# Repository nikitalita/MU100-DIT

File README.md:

# MU100-DIT

A modification for Yamaha synthesizers to add optical audio out.

This mod has been especially designed for: 
* Yamaha MU100
* Yamaha MU100R
* Yamaha MU90
* Yamaha MU90R

For these synths, a connector board has been designed that enables this mod to be installed with little-to-no board modification.

On the MU100/MU90, this involves soldering an unpopulated header and bridging some pads.

On the Rackmount versions of these, the MU100R/MU90R, this will plug in directly to the molex connector for the analog board, no board modification required:

The main board has been designed to fit within the limited back panel space on the MU100/MU90 and to not run into the MU100/MU100R's expansion cards.

## Schematics:

### Main board

### MU100/MU90 Connector board

## Installation instructions:

For the Yamaha MU100/MU90, the DIF0 must be bridged, all others left floating.

**TODO: Rest of instructions**

## Other compatible synths
This includes the following synthesizers:

* Yamaha MU128
* Yamaha AN200

...and many others. This mod will work for any device that has a 16-bit, 18-bit, 20-bit, or 24-bit PCM/I2S data stream feeding into the DAC, and has a consistent sample rate of 32/44.1/48/88.2/96khz. If you would like to test this out on other devices, please feel free to submit a pull request detailing what device and what settings you set.

## Links:
* https://esher.ru/blog/887.html - The main inspiration for this design, special thanks to vetal!
* https://github.com/vetal-esher/18bit-DIT - Vetal's custom AK4103A board that is designed to use coax with a transformer instead of optical.
* https://kurohane.net/wiki/index.php?SC-88Pro%E3%81%AB%E5%85%89%E3%83%87%E3%82%B8%E3%82%BF%E3%83%AB%E5%87%BA%E5%8A%9B%E3%82%92%E4%BB%98%E3%81%91%E3%82%8B (Japanese) - Another AK4103A optical mod, designed for the SC-88 pro.
* https://github.com/w-dee/AK4103A-DIT - Another, general purpose AK4103A DIT modification.

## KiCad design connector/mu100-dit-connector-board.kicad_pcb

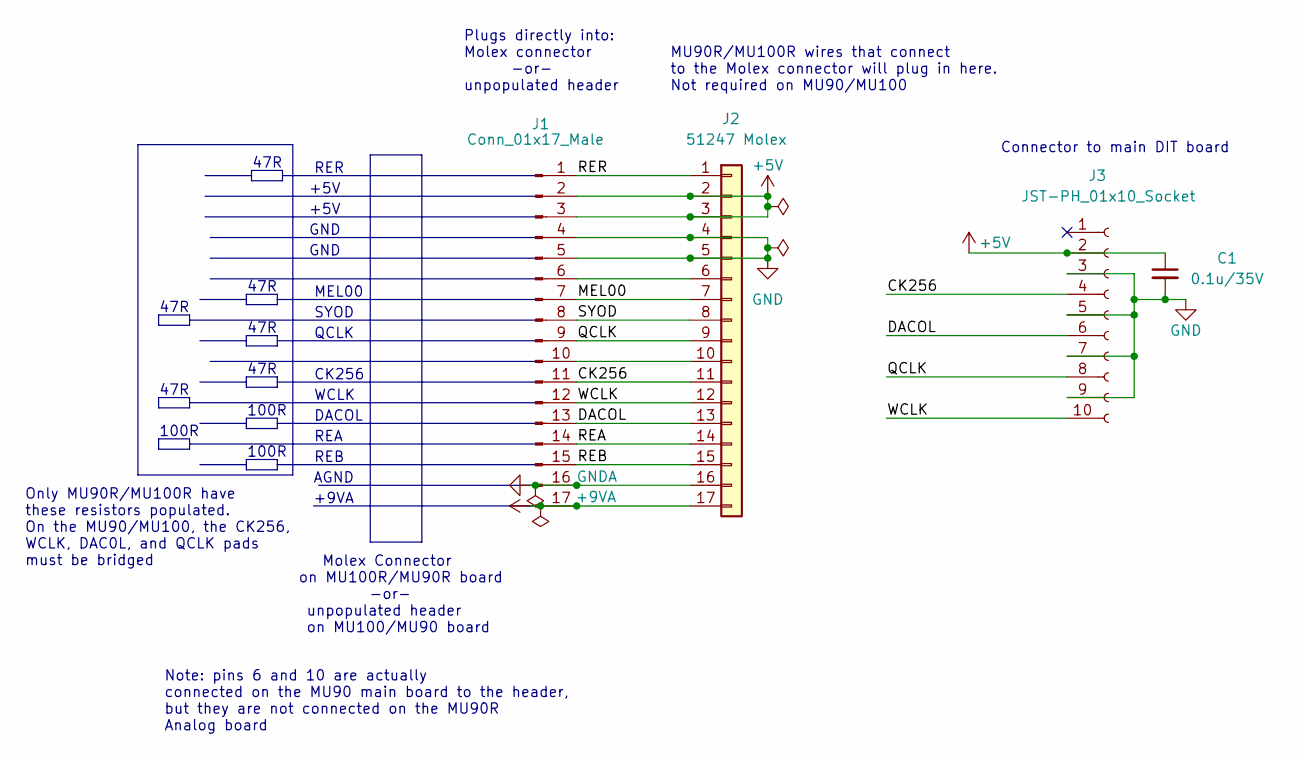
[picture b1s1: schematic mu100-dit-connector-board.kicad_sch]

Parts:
C1: 0.1u/35V; C_0805_2012Metric_Pad1.18x1.45mm_HandSolder
J1: Conn_01x17_Male; PinHeader_1x17_P2.00mm_Vertical
J2: 51247 Molex; Molex_Wire-Trap_52147-1710_1x17_P2.00mm_Vertical; Mfg. Part No. 0521471710; Mouser 538-52147-1710
J3: JST-PH_01x10_Socket; JST_PH_B10B-PH-K_1x10_P2.00mm_Vertical

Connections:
+5V: C1.1, J1.2, J1.3, J2.2, J2.3, J3.2
+9VA: J1.17, J2.17
/CK256: J1.11, J2.11, J3.4
/DACOL: J1.13, J2.13, J3.6
/MEL00: J1.7, J2.7
/QCLK: J1.9, J2.9, J3.8
/REA: J1.14, J2.14
/REB: J1.15, J2.15
/RER: J1.1, J2.1
/SYOD: J1.8, J2.8
/WCLK: J1.12, J2.12, J3.10
GND: C1.2, J1.4, J1.5, J2.4, J2.5, J3.3, J3.5, J3.7, J3.9
GNDA: J1.16, J2.16
unnamed: J1.6, J2.6
unnamed: J1.10, J2.10

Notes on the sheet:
100R
Only MU90R/MU100R have these resistors populated. On the MU90/MU100, the CK256, WCLK, DAC0L, and QCLK pads must be bridged
+5V
Note: pins 6 and 10 are actually connected on the MU90 main board to the header, but they are not connected on the MU90R Analog board
REB
47R
+9VA
CK256
SYOD
DACOL
GND
QCLK
Plugs directly into: Molex connector -or- unpopulated header
Molex Connector on MU100R/MU90R board -or- unpopulated header on MU100/MU90 board
MEL00
REA
RER
Connector to main DIT board
AGND
WCLK
MU90R/MU100R wires that connect to the Molex connector will plug in here. Not required on MU90/MU100

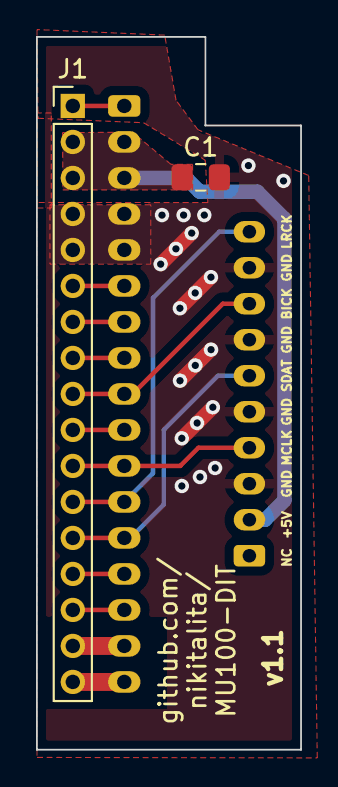
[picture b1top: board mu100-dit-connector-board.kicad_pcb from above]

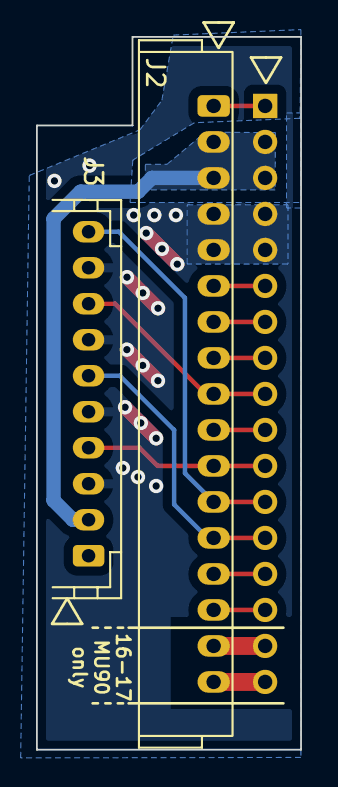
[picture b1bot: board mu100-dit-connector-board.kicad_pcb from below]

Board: 2 copper layers, 14.7 x 39.6 mm, 4 parts (2 on the bottom side), 15 nets.

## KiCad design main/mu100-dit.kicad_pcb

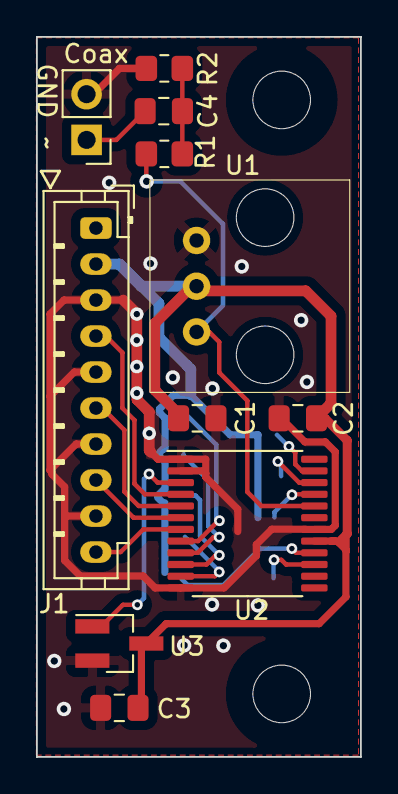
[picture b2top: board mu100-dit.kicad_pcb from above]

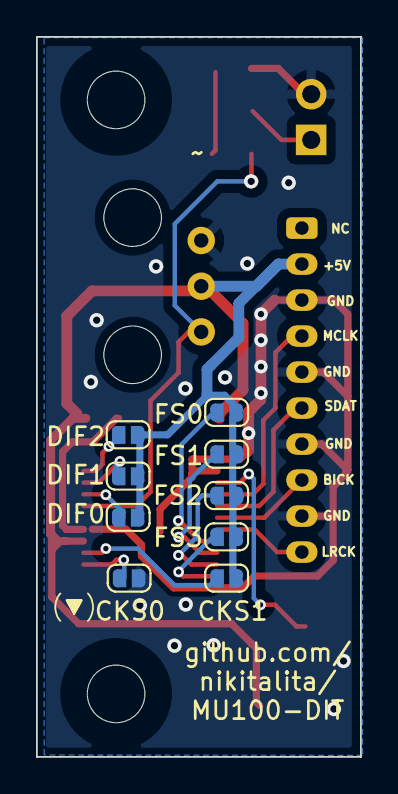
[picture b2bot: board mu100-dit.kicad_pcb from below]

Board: 2 copper layers, 18.0 x 40.0 mm, 22 parts (9 on the bottom side), 19 nets.

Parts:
C1, C2, C3, C4: 0.1uF; C_0805_2012Metric_Pad1.18x1.45mm_HandSolder
H1, H2: MountingHole_Pad; MountingHole_3.2mm_M3_ISO7380
J1: Conn_01x10_Female; JST_PH_B10B-PH-K_1x10_P2.00mm_Vertical
J2: Conn_01x02_Male; PinHeader_1x02_P2.54mm_Vertical
JP1, JP2, JP3, JP4, JP5, JP6, JP7, JP8, JP9: Jumper_NO_Small; SolderJumper-Open_RoundedPad-custom
R1: 330; R_0805_2012Metric_Pad1.20x1.40mm_HandSolder
R2: 100; R_0805_2012Metric_Pad1.20x1.40mm_HandSolder
U1: TOTX-177L; Toshiba_TOTX177
U2: AK4103A; TSSOP-24_6.1x7.8mm_P0.65mm
U3: APX809S-46SR-7; SOT-23_Handsoldering

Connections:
+5V: C1.2, C2.2, C3.2, J1.2, JP1.1, JP2.1, JP3.1, JP4.1, JP5.1, JP6.1, JP7.1, JP9.1, U1.2 (VCC), U2.17 (VDD), U3.3 (VCC)
/BICK: J1.8, U2.6 (BICK)
/CKS0: JP8.2, U2.15 (CKS0)
/CKS1: JP9.2, U2.16 (CKS1)
/DIF0: JP5.2, U2.21 (DIF0)
/DIF1: JP6.2, U2.22 (DIF1)
/DIF2: JP7.2, U2.23 (DIF2)
/FS0: JP1.2, U2.8 (FS0/CSN)
/FS1: JP2.2, U2.9 (FS1/CDTI)
/FS2: JP3.2, U2.10 (FS2/CCLK)
/FS3: JP4.2, U2.11 (FS3/CDTO)
/LRCK: J1.10, U2.7 (LRCK)
/MCLK: J1.4, U2.4 (MCLK)
/RESET: U2.3 (PDN), U3.1 (~RESET)
/SDAT: J1.6, U2.5 (SDTI)
/TXP: R1.1, U1.3 (Input), U2.20 (TXP)
GND: C1.1, C2.1, C3.1, J1.3, J1.5, J1.7, J1.9, J2.2, JP8.1, R2.1, U1.1 (GND), U2.1 (V1), U2.2 (TRANS), U2.12 (C1), U2.18 (VSS), U3.2 (GND)
unnamed: C4.1, R1.2, R2.2
unnamed: C4.2, J2.1

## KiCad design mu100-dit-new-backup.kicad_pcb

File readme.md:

From https://kurohane.net/wiki/index.php?SC-88Pro%E3%81%AB%E5%85%89%E3%83%87%E3%82%B8%E3%82%BF%E3%83%AB%E5%87%BA%E5%8A%9B%E3%82%92%E4%BB%98%E3%81%91%E3%82%8B

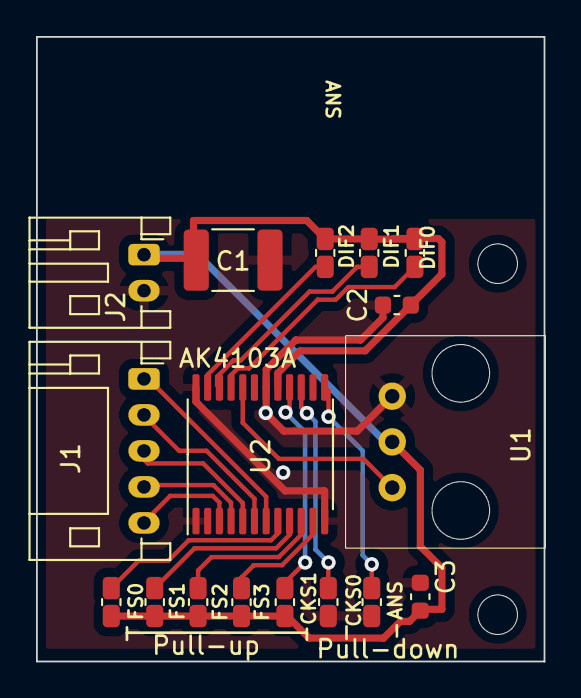
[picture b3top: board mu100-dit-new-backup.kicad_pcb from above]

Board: 2 copper layers, 28.2 x 34.7 mm, 17 parts (0 on the bottom side), 18 nets.

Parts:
C1: 33u/16v; C_1812_4532Metric
C2, C3: 0.1u/35V; C_0603_1608Metric
J1: Conn_01x05_Male; JST_PH_S5B-PH-K_1x05_P2.00mm_Horizontal
J2: Conn_01x02_Male; JST_PH_S2B-PH-K_1x02_P2.00mm_Horizontal
JP1, JP2, JP3, JP9, JP11, JP14, JP15, JP16, JP17, JP18: Jumper_NO_Small; R_0603_1608Metric_SolderJumperCompatible
U1: TOTX-177L; Toshiba_TOTX177
U2: AK4103A; TSSOP-24_6.1x7.8mm_P0.65mm

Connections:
+5V: C1.1, C2.2, C3.2, J2.1, JP1.1, JP2.1, JP3.1, JP11.1, JP14.1, JP15.1, JP17.1, JP18.1, U1.2 (VCC), U2.17 (VDD)
/ANS: JP16.1, U2.13 (ANS)
/BICK: J1.2, U2.6 (BICK)
/CCLK: JP17.2, U2.10 (FS2/CCLK)
/CDTI: JP15.2, U2.9 (FS1/CDTI)
/CDTO: JP18.2, U2.11 (FS3/CDTO)
/CKS0: JP9.2, U2.15 (CKS0)
/CKS1: JP11.2, U2.16 (CKS1)
/CSN: JP14.2, U2.8 (FS0/CSN)
/DIF0: JP1.2, U2.21 (DIF0)
/DIF1: JP2.2, U2.22 (DIF1)
/DIF2: JP3.2, U2.23 (DIF2)
/LRCK: J1.1, U2.7 (LRCK)
/MCLK: J1.4, U2.4 (MCLK)
/RESET: J1.5, U2.3 (PDN)
/SDAT: J1.3, U2.5 (SDTI)
/TXP: U1.1 (GND), U2.20 (TXP)
GND: C1.2, C2.1, C3.1, J2.2, JP9.1, JP16.2, U1.3 (Input), U2.1 (V1), U2.2 (TRANS), U2.12 (C1), U2.18 (VSS), U2.24 (U1)

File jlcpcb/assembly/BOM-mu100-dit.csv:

Comment,Designator,Footprint,LCSC
Conn_01x02_Male,J2,JST_PH_S2B-PH-K_1x02_P2.00mm_Horizontal,
AK4103A,U2,TSSOP-24_6.1x7.8mm_P0.65mm,
TOTX-177L,U1,Toshiba_TOTX177,
0.1u/35V,C2,C_0805_2012Metric_Pad1.18x1.45mm_HandSolder,
Conn_01x05_Male,J1,JST_PH_S5B-PH-K_1x05_P2.00mm_Horizontal,
0.1u/35V,C1,C_0805_2012Metric_Pad1.18x1.45mm_HandSolder,

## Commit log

2022-07-01 fix readme
2022-07-01 remove backups
2022-07-01 remove temp files
2022-07-01 fix issue with totx177 footprint, fix schematics
2022-07-01 update gerbers
2022-07-01 add jumpers to board
2022-07-02 Add connector board
2022-07-03 Add reset circuit, remove need for reset
2022-07-03 Update screw hole position
2022-07-03 Move reset circuit to other side of board
2022-07-04 Add header for optional coax output
2022-07-04 finish connector pcb
2022-07-05 combine pcb projects
2022-07-05 fix coax placement
2022-07-17 undo merge, panelize connector board
2022-07-17 Cleanup files, no board changes
2022-07-17 Add schematics
2022-07-17 Clean up schematics and board drawings
2022-07-20 Unground mounting holes, rearrange DIF0/DIF1 vias to avoid bridge
2022-07-27 minor tweaks to main board
2022-07-28 remove terminating resistors on connector board
2022-09-02 FInal board revision
